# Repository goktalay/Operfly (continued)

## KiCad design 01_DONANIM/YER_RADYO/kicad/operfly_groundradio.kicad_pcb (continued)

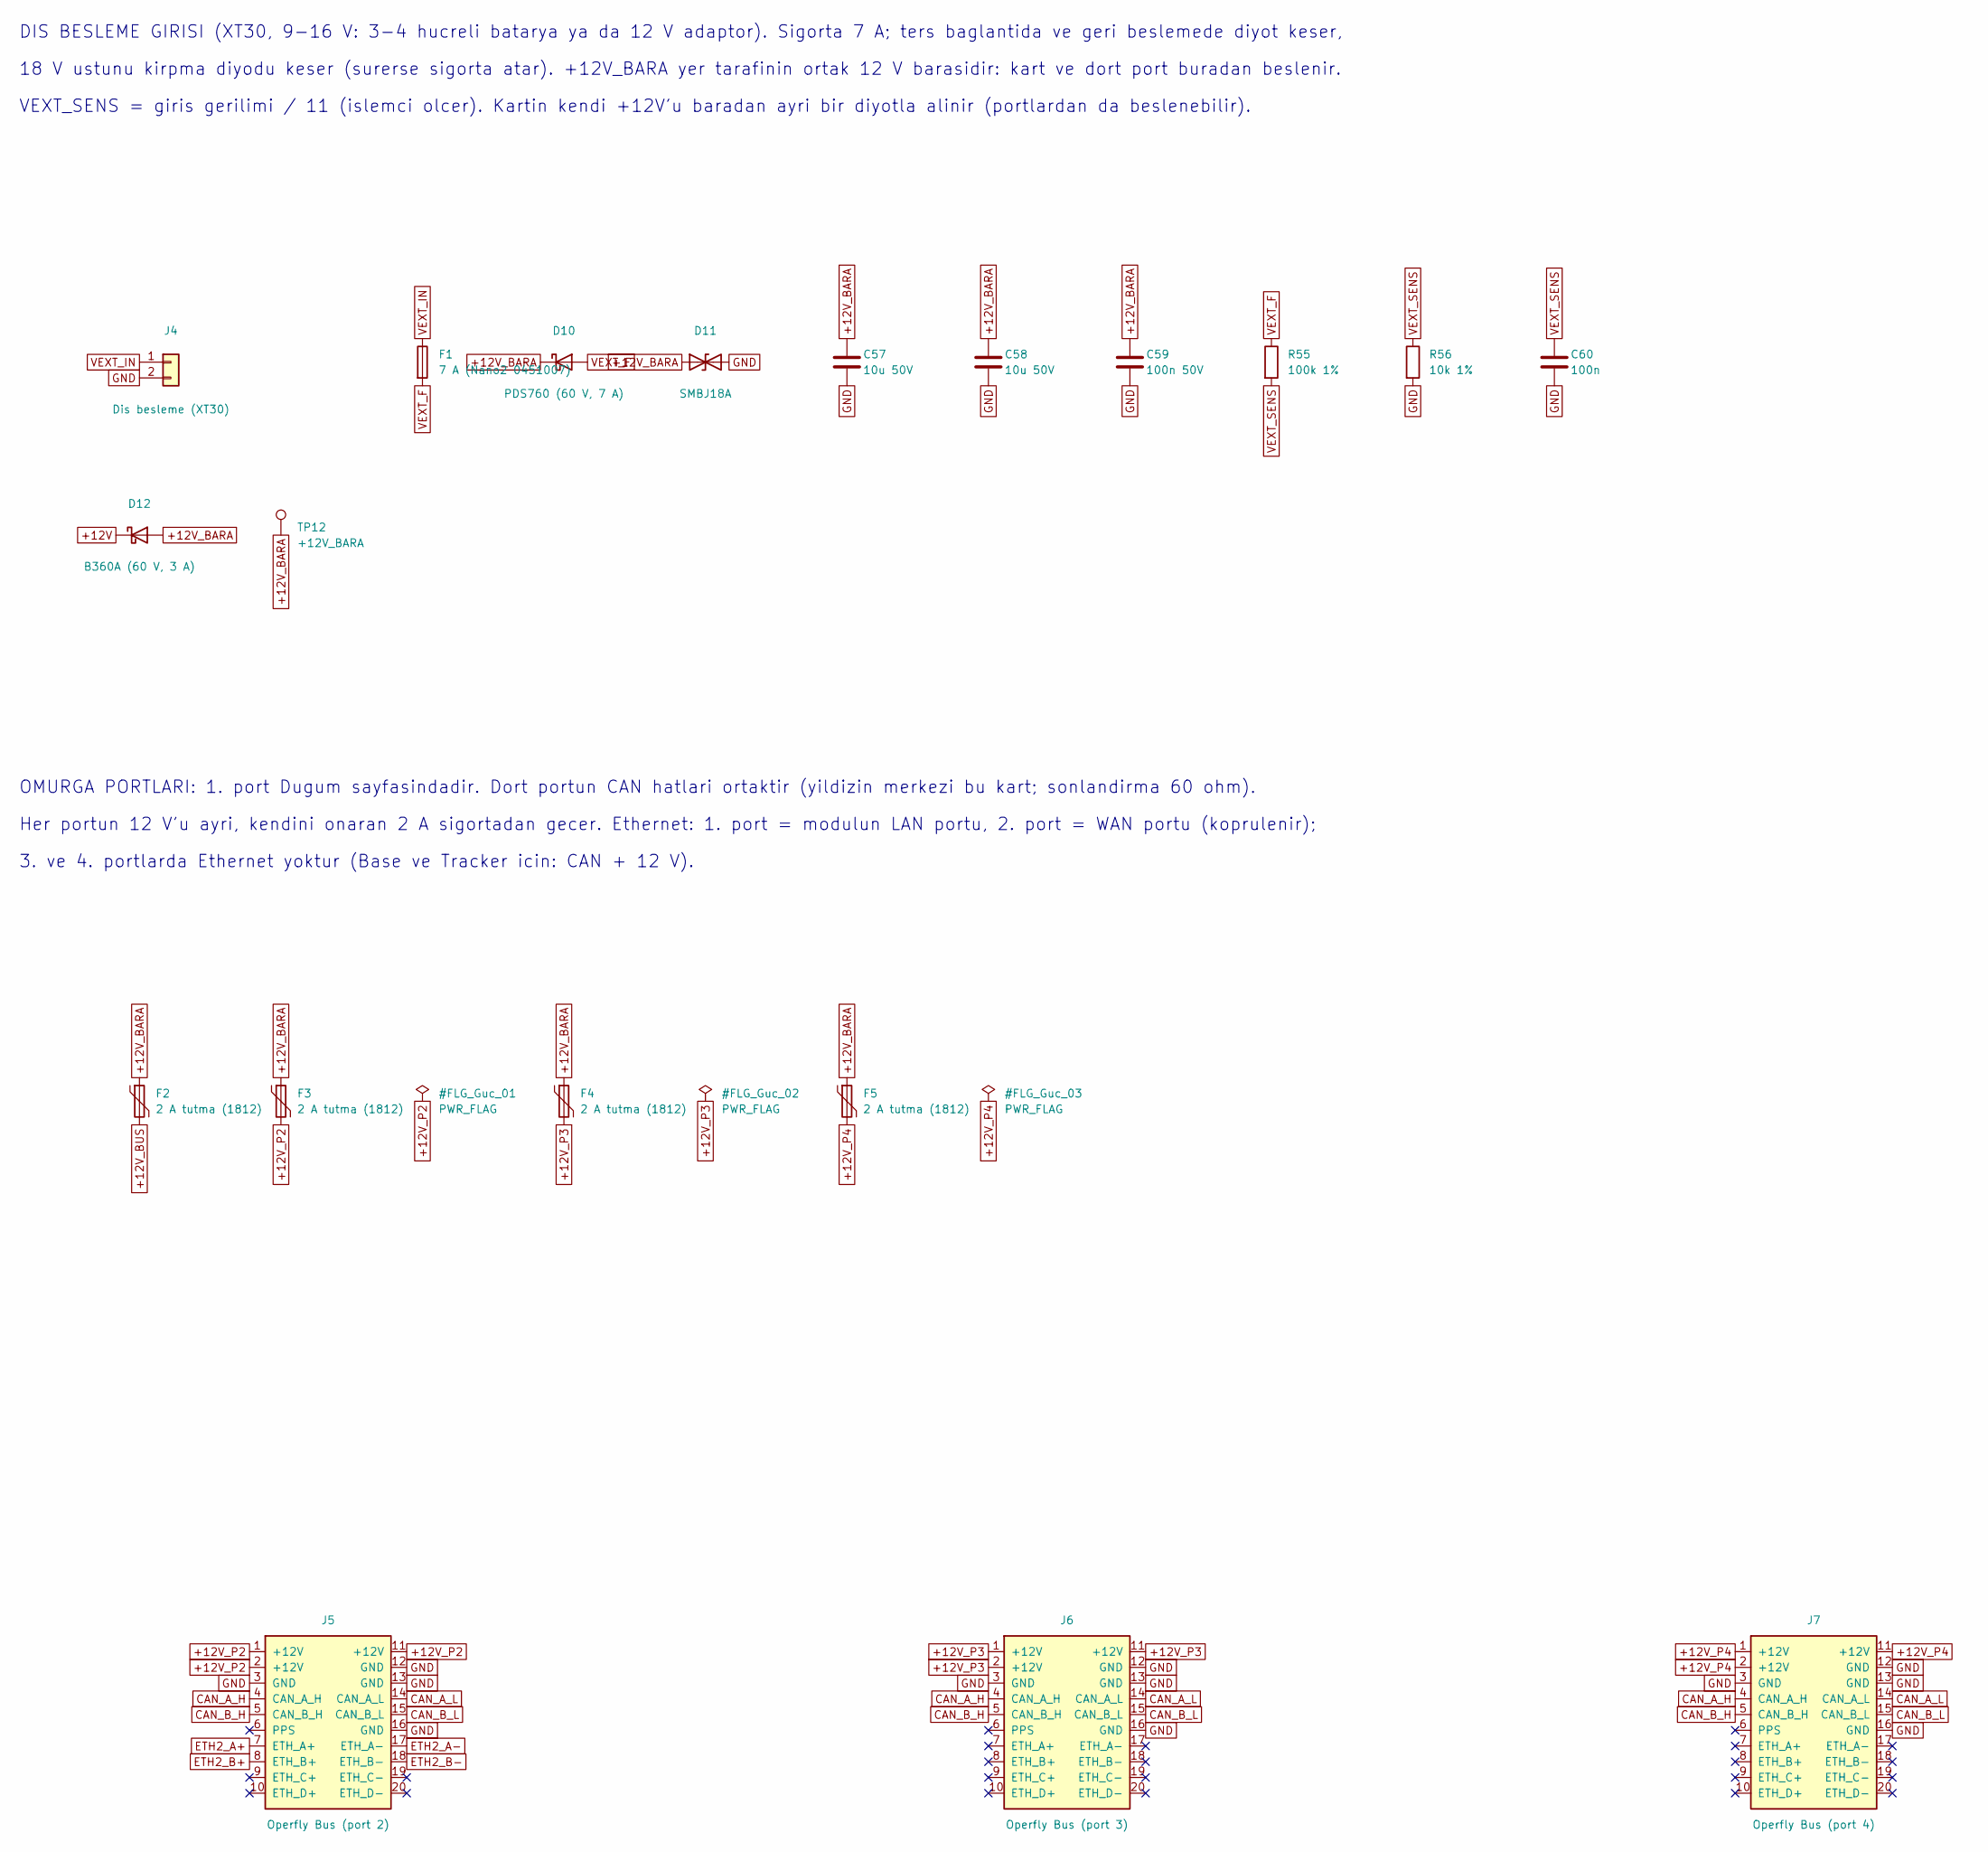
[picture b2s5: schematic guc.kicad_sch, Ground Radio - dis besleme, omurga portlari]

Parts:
C57, C58: 10u 50V; C_1206_3216Metric
C59: 100n 50V; C_0603_1608Metric
C60: 100n; C_0402_1005Metric
D10: PDS760 (60 V, 7 A); D_PowerDI-5
D11: SMBJ18A; D_SMB
D12: B360A (60 V, 3 A); D_SMA
F1: 7 A (Nano2 0451007); Fuse_Littelfuse-NANO2-451_453
F2, F3, F4, F5: 2 A tutma (1812); Fuse_1812_4532Metric
J4: Dis besleme (XT30); AMASS_XT30U-M_1x02_P5.0mm_Vertical
J5: Operfly Bus (port 2); Harwin_Gecko_G125-MS12005M2P_2x10_P1.25mm_Vertical
J6: Operfly Bus (port 3); Harwin_Gecko_G125-MS12005M2P_2x10_P1.25mm_Vertical
J7: Operfly Bus (port 4); Harwin_Gecko_G125-MS12005M2P_2x10_P1.25mm_Vertical
R55: 100k 1%; R_0402_1005Metric
R56: 10k 1%; R_0402_1005Metric
TP12: +12V_BARA; TestPoint_Pad_D1.0mm

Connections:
+12V: D12.1 (K); also elsewhere on the board
+12V_BARA: C57.1, C58.1, C59.1, D10.1 (K), D11.1 (A1), D12.2 (A), F2.1, F3.1, F4.1, F5.1, TP12.1
+12V_BUS: F2.2; also elsewhere on the board
+12V_P2: F3.2, J5.1 (+12V), J5.2 (+12V), J5.11 (+12V)
+12V_P3: F4.2, J6.1 (+12V), J6.2 (+12V), J6.11 (+12V)
+12V_P4: F5.2, J7.1 (+12V), J7.2 (+12V), J7.11 (+12V)
CAN_A_H: J5.4 (CAN_A_H), J6.4 (CAN_A_H), J7.4 (CAN_A_H); also elsewhere on the board
CAN_A_L: J5.14 (CAN_A_L), J6.14 (CAN_A_L), J7.14 (CAN_A_L); also elsewhere on the board
CAN_B_H: J5.5 (CAN_B_H), J6.5 (CAN_B_H), J7.5 (CAN_B_H); also elsewhere on the board
CAN_B_L: J5.15 (CAN_B_L), J6.15 (CAN_B_L), J7.15 (CAN_B_L); also elsewhere on the board
ETH2_A+: J5.7 (ETH_A+); also elsewhere on the board
ETH2_A-: J5.17 (ETH_A-); also elsewhere on the board
ETH2_B+: J5.8 (ETH_B+); also elsewhere on the board
ETH2_B-: J5.18 (ETH_B-); also elsewhere on the board
GND: C57.2, C58.2, C59.2, C60.2, D11.2 (A2), J4.2, J5.3 (GND), J5.12 (GND), J5.13 (GND), J5.16 (GND), J6.3 (GND), J6.12 (GND), J6.13 (GND), J6.16 (GND), J7.3 (GND), J7.12 (GND), J7.13 (GND), J7.16 (GND), R56.2; also elsewhere on the board
VEXT_F: D10.2 (A), F1.2, R55.1
VEXT_IN: F1.1, J4.1
VEXT_SENS: C60.1, R55.2, R56.1; also elsewhere on the board

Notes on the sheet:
VEXT_SENS = giris gerilimi / 11 (islemci olcer). Kartin kendi +12V'u baradan ayri bir diyotla alinir (portlardan da beslenebilir).
Her portun 12 V'u ayri, kendini onaran 2 A sigortadan gecer. Ethernet: 1. port = modulun LAN portu, 2. port = WAN portu (koprulenir);
18 V ustunu kirpma diyodu keser (surerse sigorta atar). +12V_BARA yer tarafinin ortak 12 V barasidir: kart ve dort port buradan beslenir.
3. ve 4. portlarda Ethernet yoktur (Base ve Tracker icin: CAN + 12 V).
DIS BESLEME GIRISI (XT30, 9-16 V: 3-4 hucreli batarya ya da 12 V adaptor). Sigorta 7 A; ters baglantida ve geri beslemede diyot keser,
OMURGA PORTLARI: 1. port Dugum sayfasindadir. Dort portun CAN hatlari ortaktir (yildizin merkezi bu kart; sonlandirma 60 ohm).

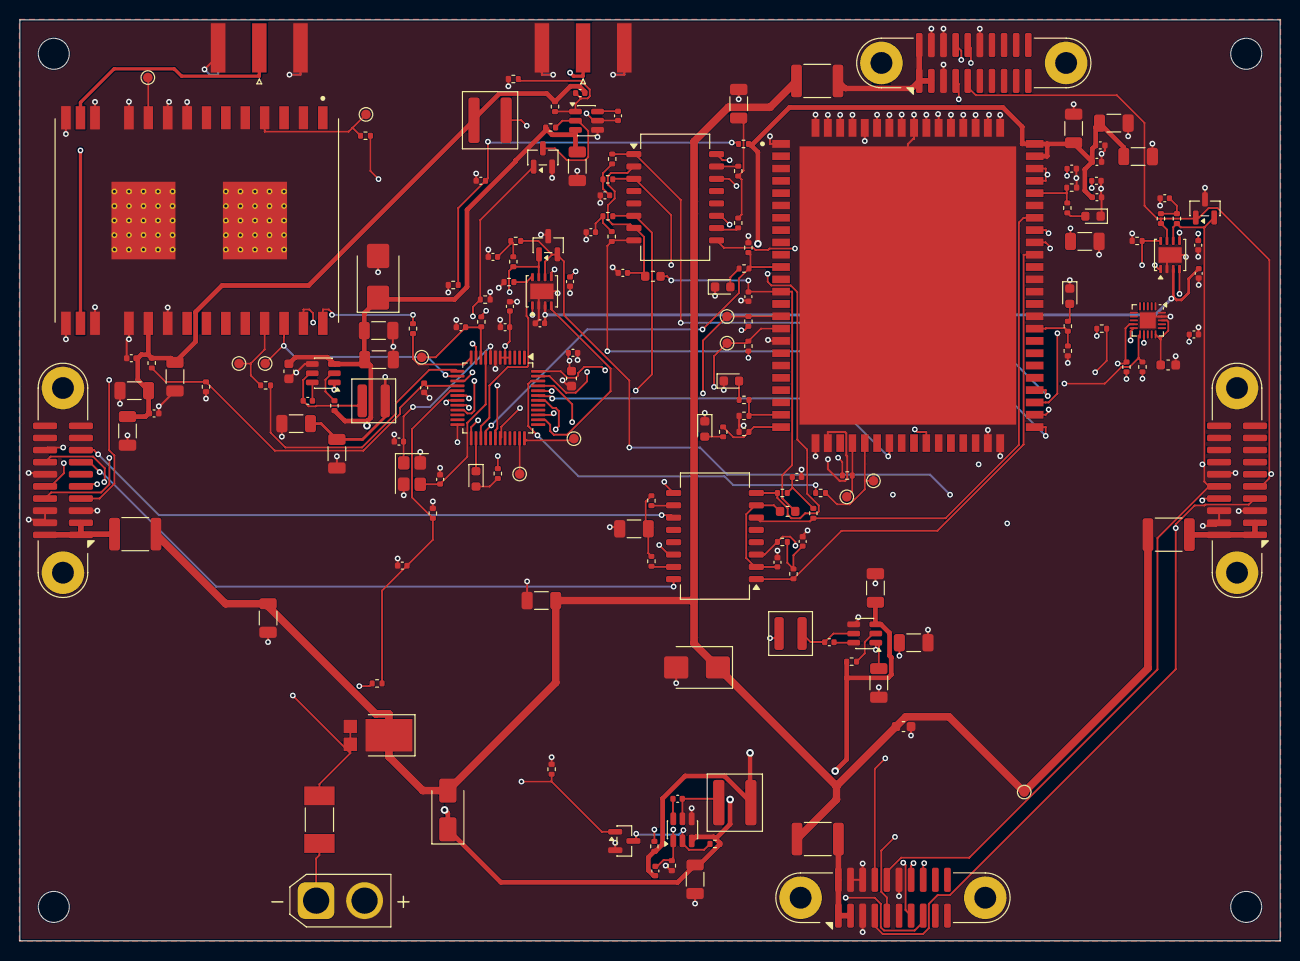
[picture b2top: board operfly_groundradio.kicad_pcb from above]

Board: 6 copper layers, 130.0 x 95.0 mm, 177 parts (0 on the bottom side), 113 nets.

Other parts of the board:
H1, H2, H3, H4: M3; MountingHole_3.2mm_M3

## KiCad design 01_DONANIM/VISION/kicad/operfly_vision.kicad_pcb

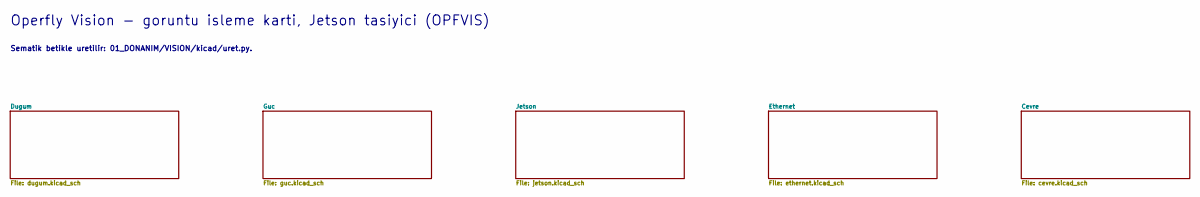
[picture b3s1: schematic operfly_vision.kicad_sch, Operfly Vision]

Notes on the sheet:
Operfly Vision - goruntu isleme karti, Jetson tasiyici (OPFVIS)
Sematik betikle uretilir: 01_DONANIM/VISION/kicad/uret.py.

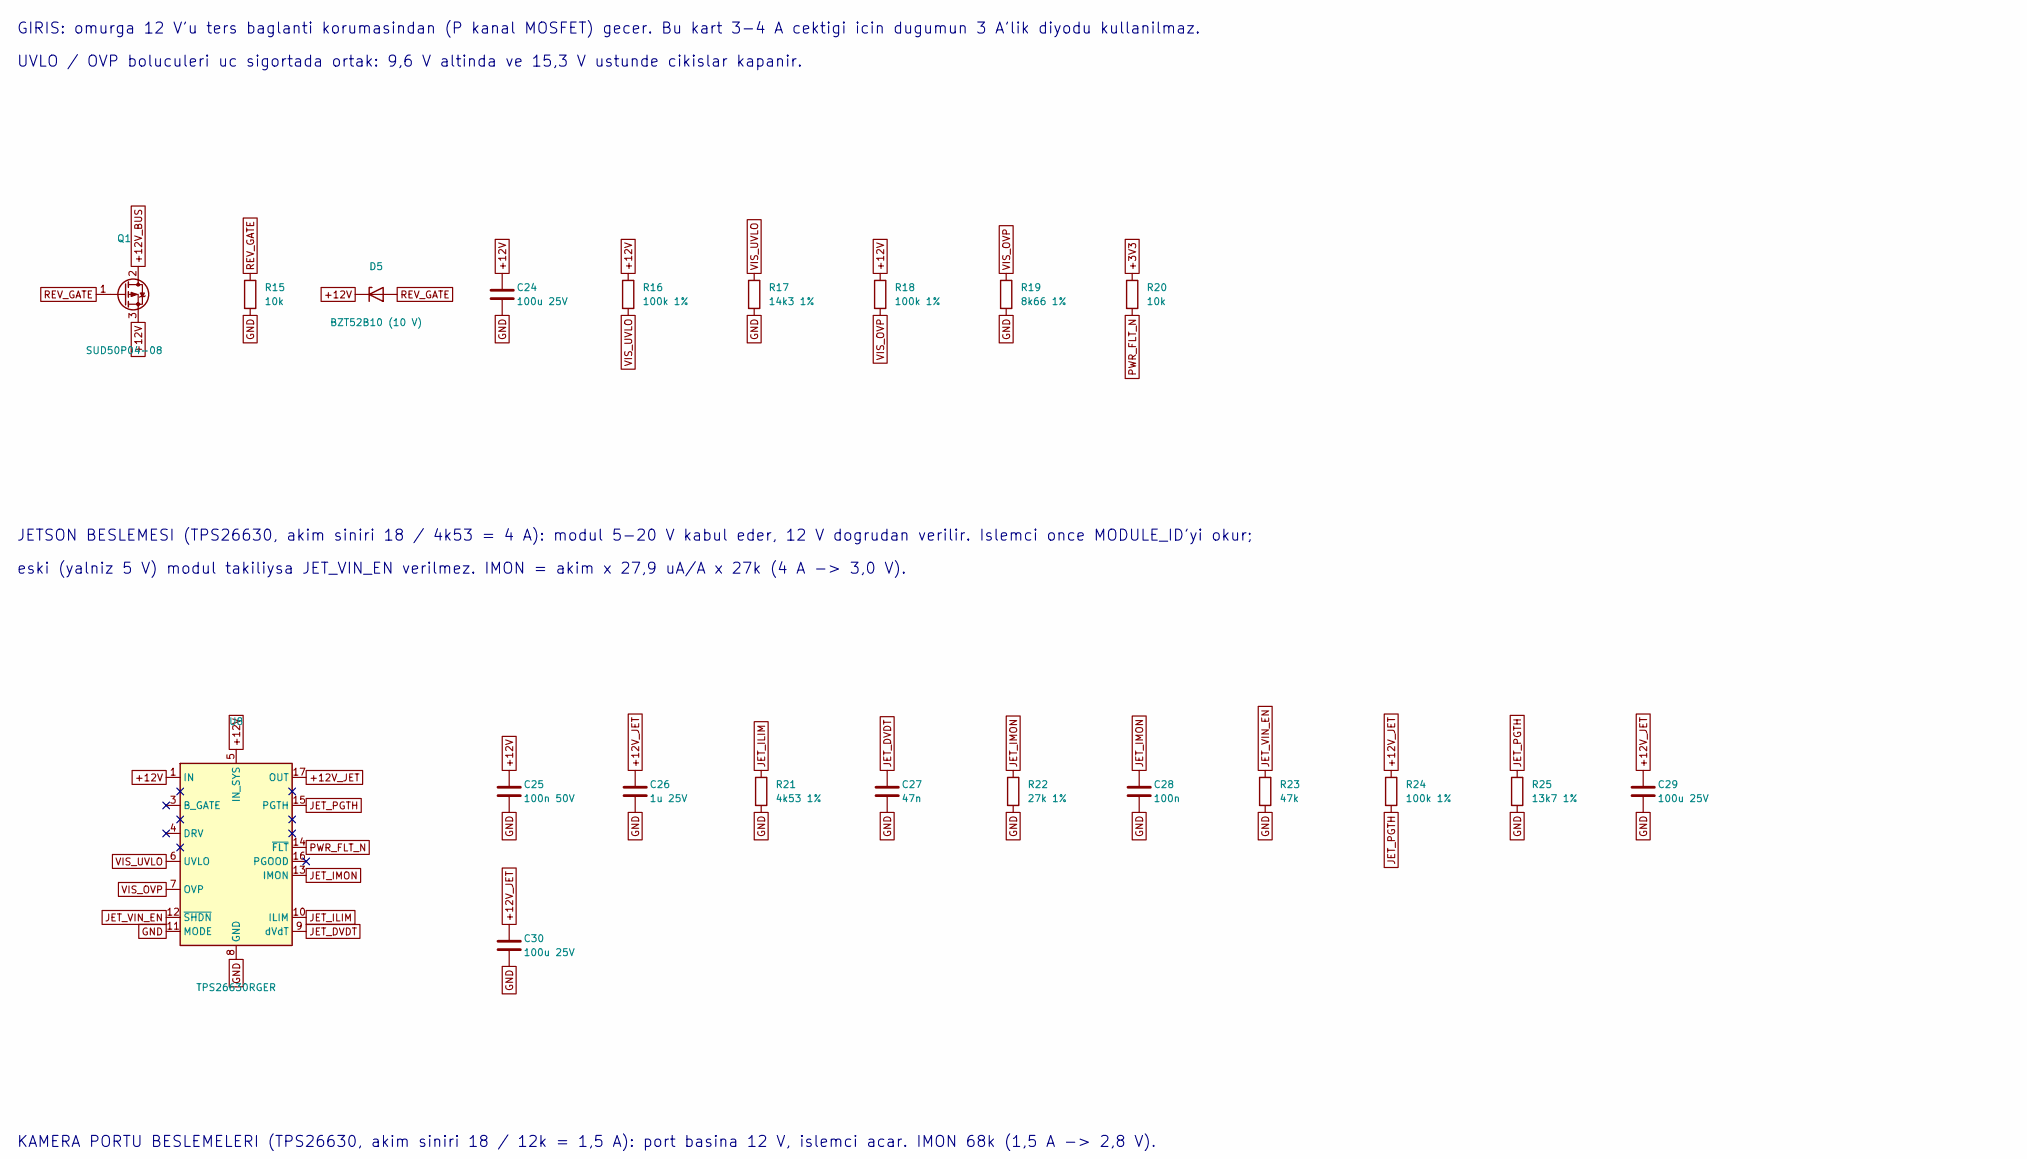
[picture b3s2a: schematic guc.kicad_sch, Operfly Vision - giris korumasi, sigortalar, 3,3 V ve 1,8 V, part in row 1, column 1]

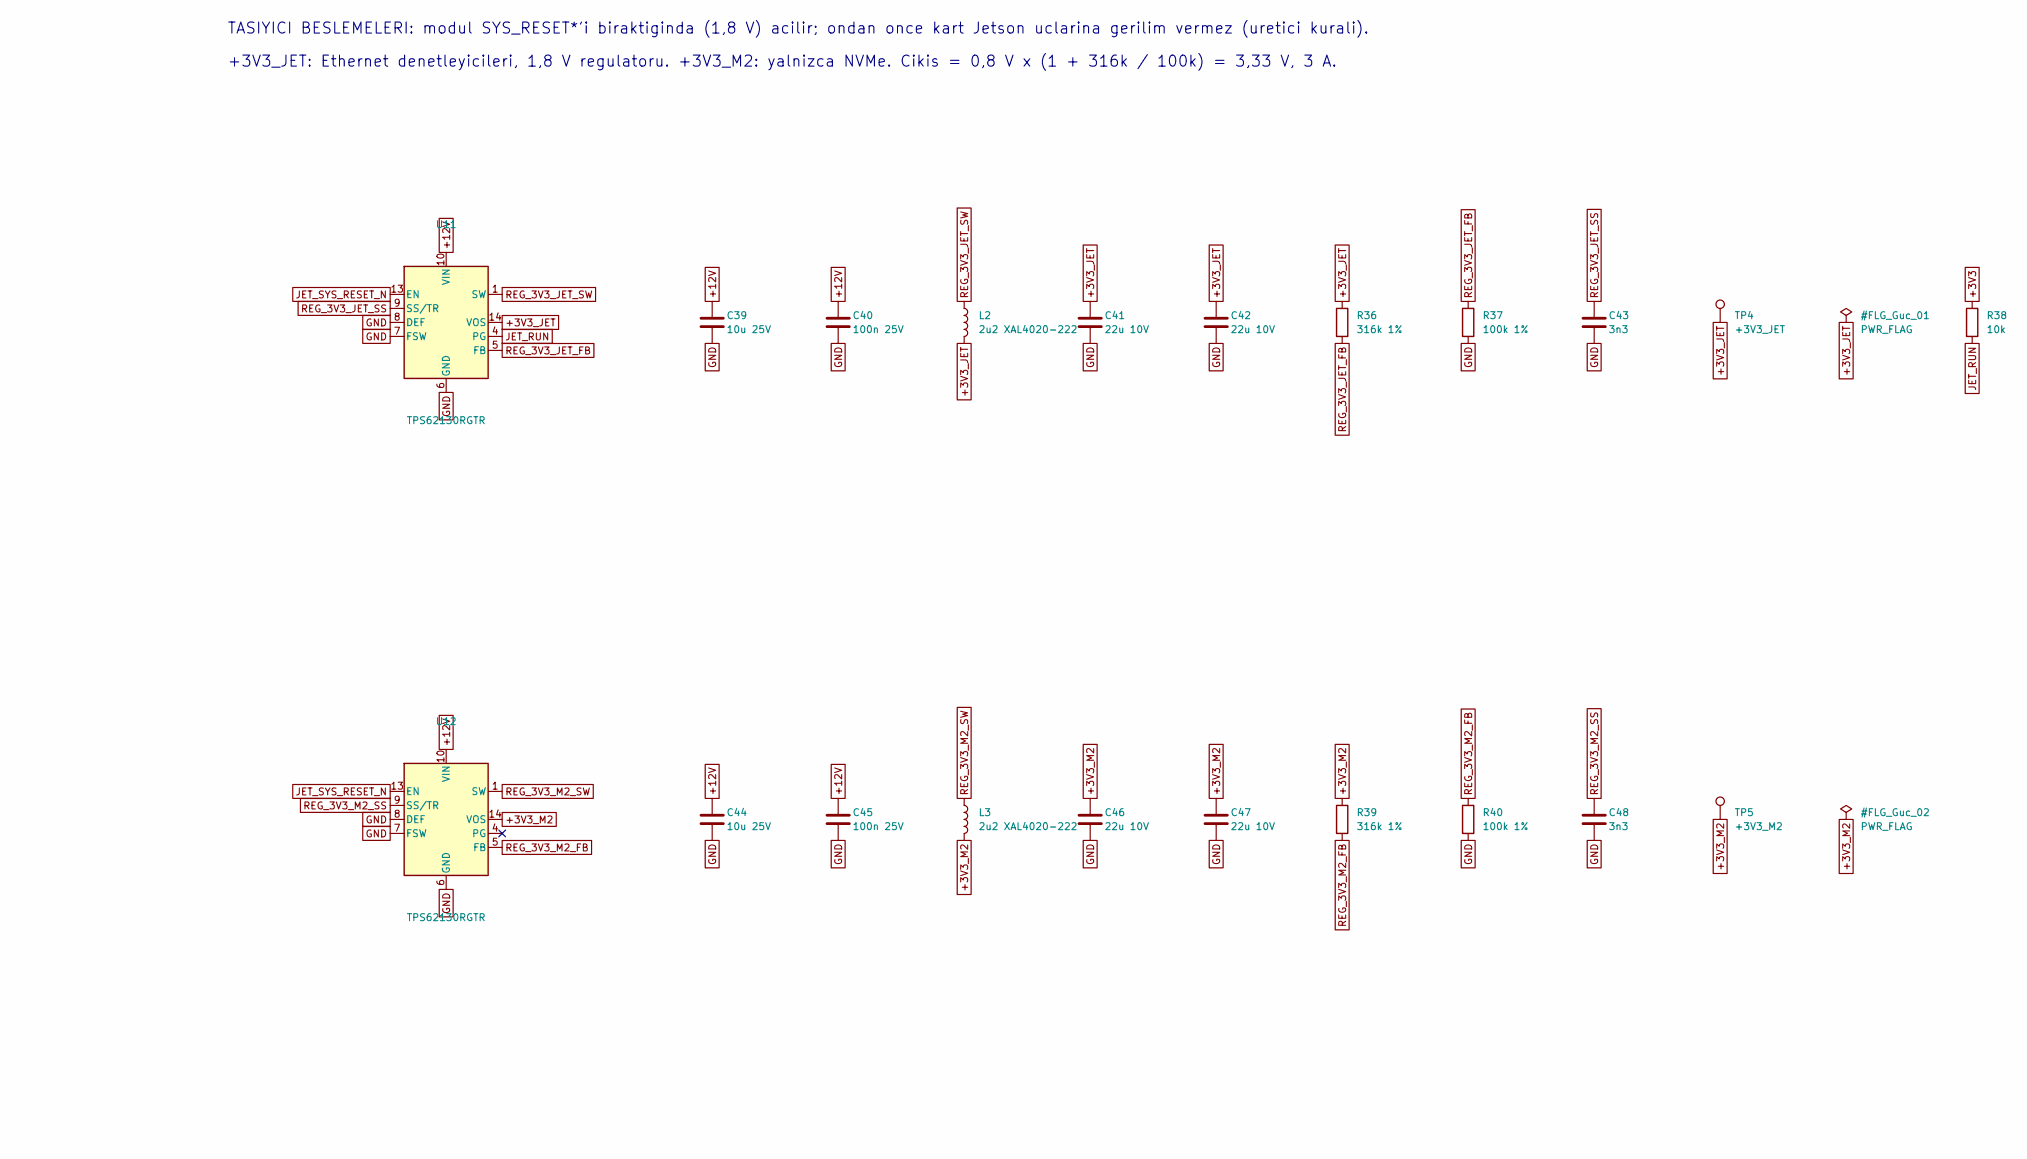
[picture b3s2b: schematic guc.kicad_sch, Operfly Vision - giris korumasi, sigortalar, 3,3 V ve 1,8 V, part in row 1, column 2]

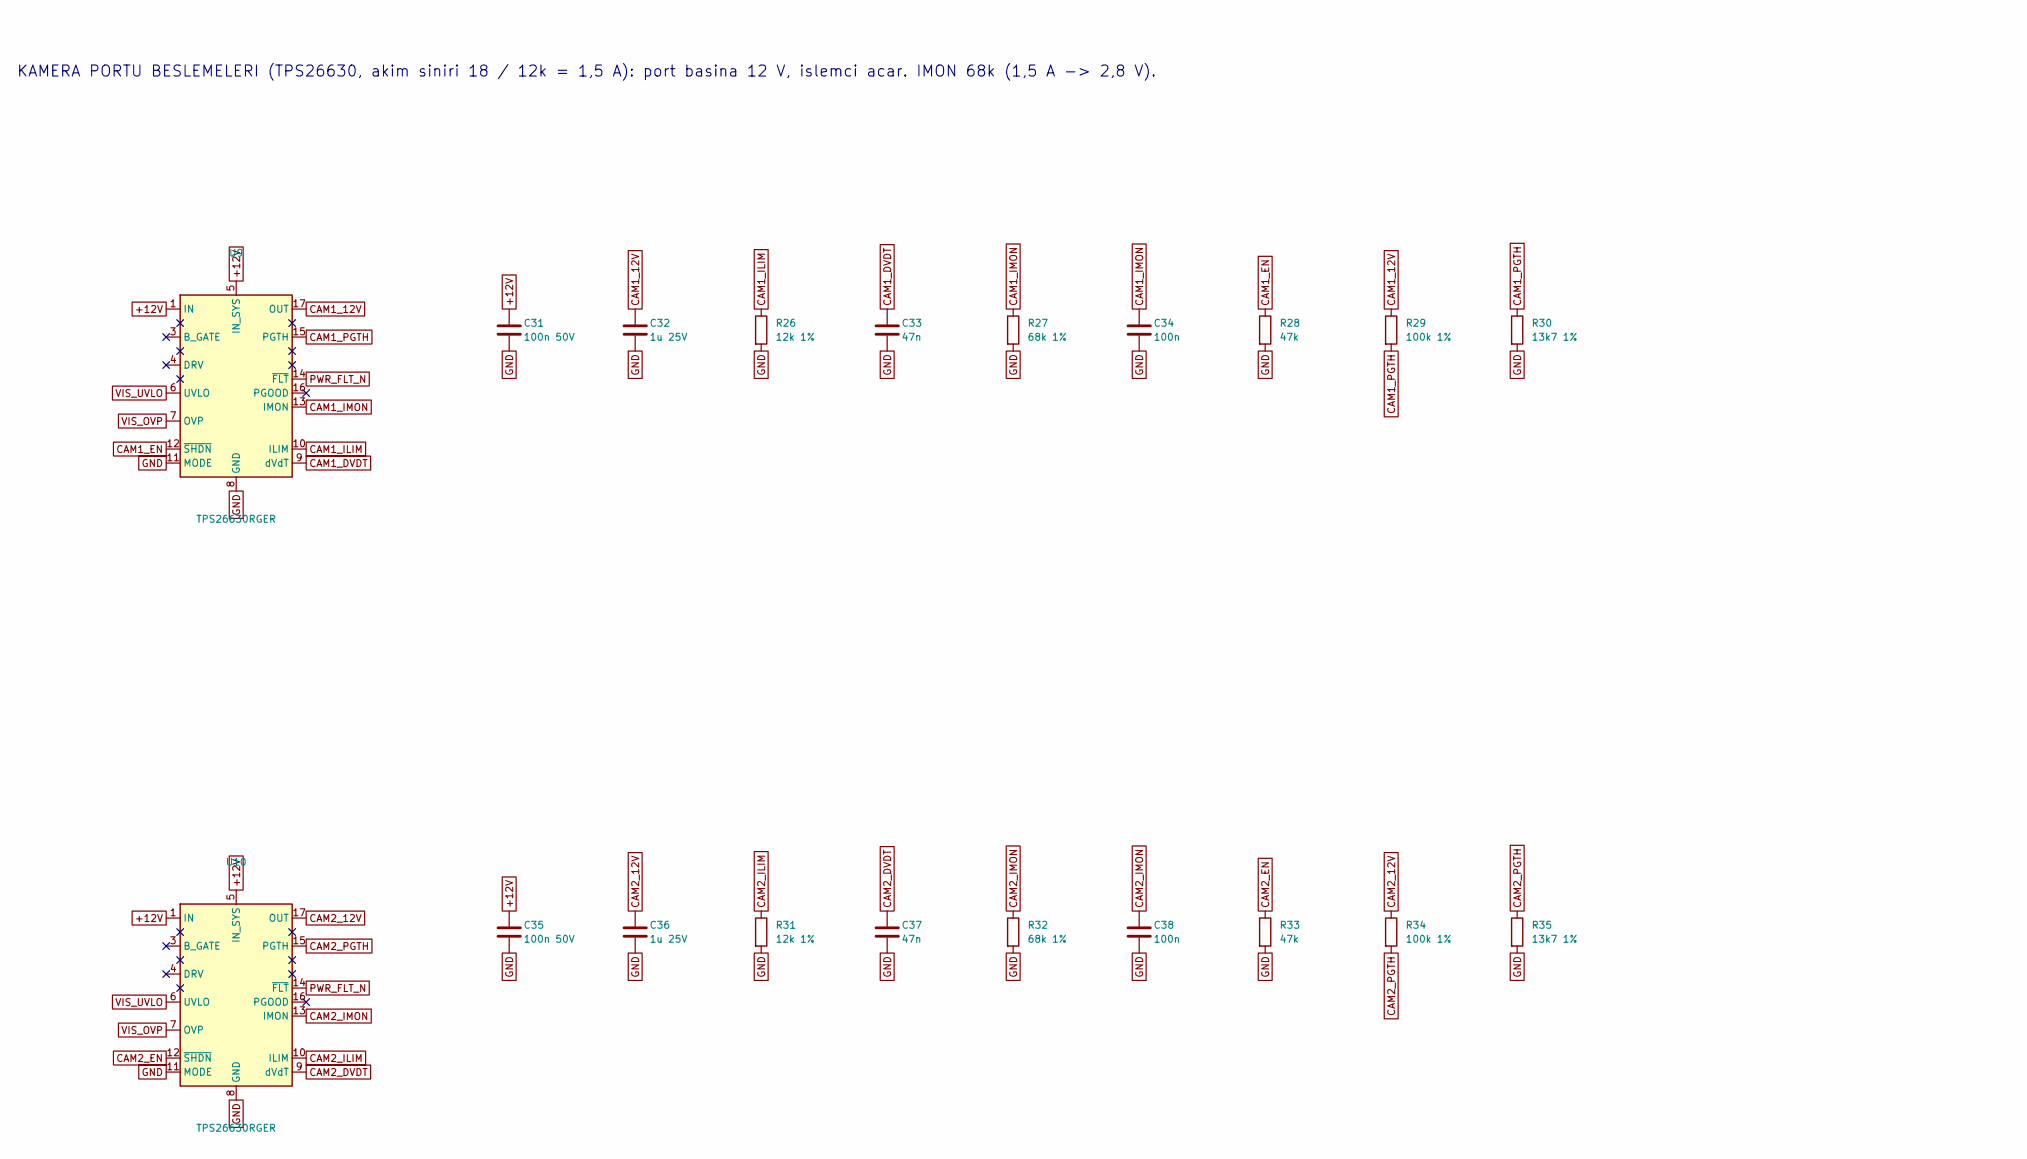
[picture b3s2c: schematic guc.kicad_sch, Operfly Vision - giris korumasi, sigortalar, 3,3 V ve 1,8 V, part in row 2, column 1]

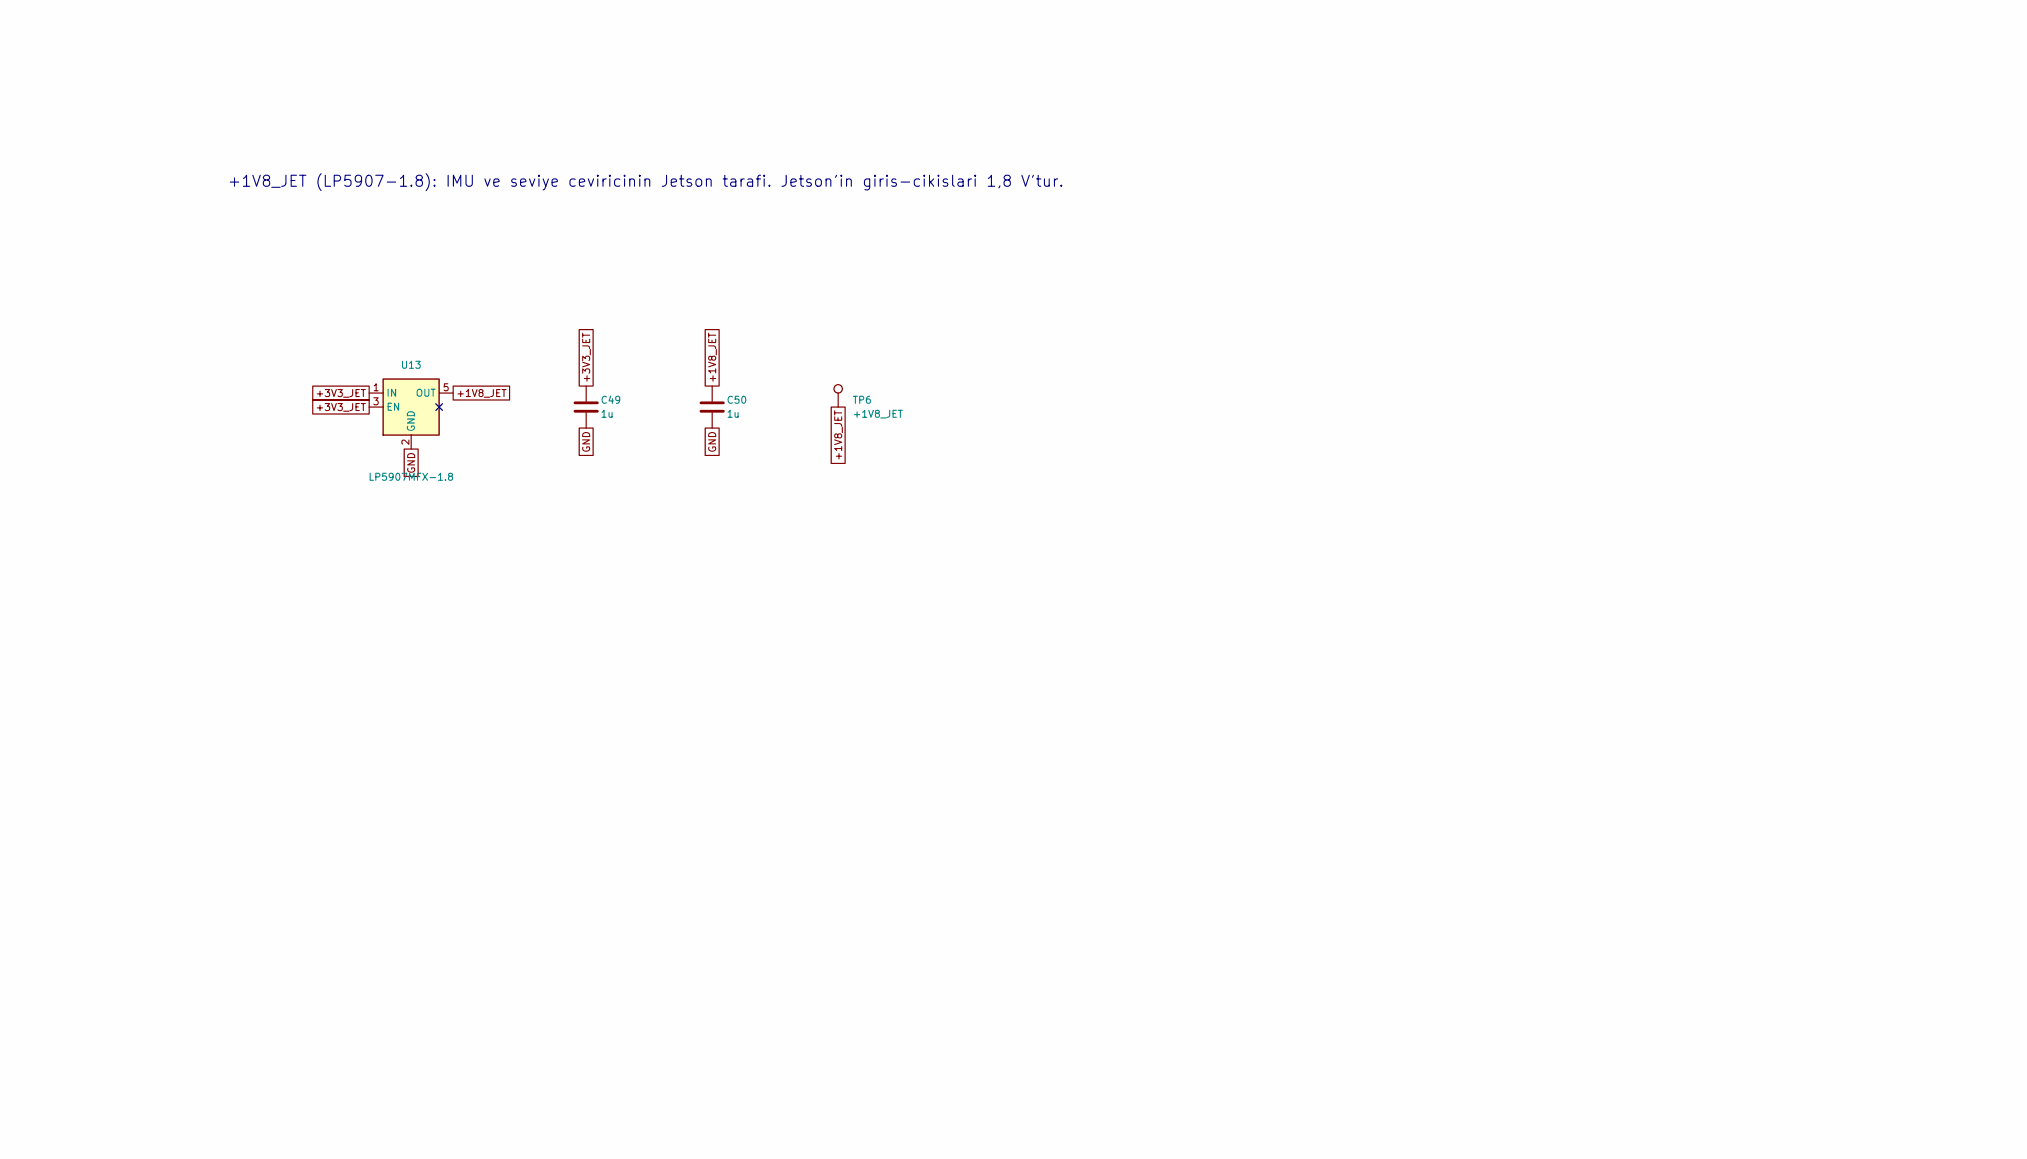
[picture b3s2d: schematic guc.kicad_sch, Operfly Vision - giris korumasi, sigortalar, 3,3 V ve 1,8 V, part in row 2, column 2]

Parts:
C24, C29, C30: 100u 25V; CP_EIA-7343-31_Kemet-D
C25, C31, C35: 100n 50V; C_0603_1608Metric
C26, C32, C36: 1u 25V; C_0603_1608Metric
C27, C33, C37: 47n; C_0402_1005Metric
C28, C34, C38: 100n; C_0402_1005Metric
C39, C44: 10u 25V; C_1206_3216Metric
C40, C45: 100n 25V; C_0603_1608Metric
C41, C42, C46, C47: 22u 10V; C_1206_3216Metric
C43, C48: 3n3; C_0402_1005Metric
C49, C50: 1u; C_0402_1005Metric
D5: BZT52B10 (10 V); D_SOD-123F
L2, L3: 2u2 XAL4020-222; L_Coilcraft_XAL4020-XXX
Q1: SUD50P04-08; TO-252-2
R15, R20, R38: 10k; R_0402_1005Metric
R16, R18, R24, R29, R34, R37, R40: 100k 1%; R_0402_1005Metric
R17: 14k3 1%; R_0402_1005Metric
R19: 8k66 1%; R_0402_1005Metric
R21: 4k53 1%; R_0402_1005Metric
R22: 27k 1%; R_0402_1005Metric
R23, R28, R33: 47k; R_0402_1005Metric
R25, R30, R35: 13k7 1%; R_0402_1005Metric
R26, R31: 12k 1%; R_0402_1005Metric
R27, R32: 68k 1%; R_0402_1005Metric
R36, R39: 316k 1%; R_0402_1005Metric
TP4: +3V3_JET; TestPoint_Pad_D1.0mm
TP5: +3V3_M2; TestPoint_Pad_D1.0mm
TP6: +1V8_JET; TestPoint_Pad_D1.0mm
U8, U9, U10: TPS26630RGER; Texas_RGE0024H_VQFN-24-1EP_4x4mm_P0.5mm_EP2.7x2.7mm_Thermal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
U11, U12: TPS62130RGTR; VQFN-16-1EP_3x3mm_P0.5mm_EP1.68x1.68mm_ThermalVias
U13: LP5907MFX-1.8; SOT-23-5

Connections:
+1V8_JET: C50.1, TP6.1, U13.5 (OUT); also elsewhere on the board
+3V3: R20.1, R38.1; also elsewhere on the board
+3V3_JET: C41.1, C42.1, C49.1, L2.2, R36.1, TP4.1, U11.14 (VOS), U13.1 (IN), U13.3 (EN); also elsewhere on the board
+3V3_M2: C46.1, C47.1, L3.2, R39.1, TP5.1, U12.14 (VOS); also elsewhere on the board
+12V: C24.1, C25.1, C31.1, C35.1, C39.1, C40.1, C44.1, C45.1, D5.1 (K), Q1.3 (S), R16.1, R18.1, U8.1 (IN), U8.2 (IN), U8.5 (IN_SYS), U9.1 (IN), U9.2 (IN), U9.5 (IN_SYS), U10.1 (IN), U10.2 (IN), U10.5 (IN_SYS), U11.10 (VIN), U11.11 (VIN), U11.12 (VIN), U12.10 (VIN), U12.11 (VIN), U12.12 (VIN); also elsewhere on the board
+12V_BUS: Q1.2 (D); also elsewhere on the board
+12V_JET: C26.1, C29.1, C30.1, R24.1, U8.17 (OUT), U8.18 (OUT); also elsewhere on the board
CAM1_12V: C32.1, R29.1, U9.17 (OUT), U9.18 (OUT); also elsewhere on the board
CAM1_DVDT: C33.1, U9.9 (dVdT)
CAM1_EN: R28.1, U9.12 (~SHDN); also elsewhere on the board
CAM1_ILIM: R26.1, U9.10 (ILIM)
CAM1_IMON: C34.1, R27.1, U9.13 (IMON); also elsewhere on the board
CAM1_PGTH: R29.2, R30.1, U9.15 (PGTH)
CAM2_12V: C36.1, R34.1, U10.17 (OUT), U10.18 (OUT); also elsewhere on the board
CAM2_DVDT: C37.1, U10.9 (dVdT)
CAM2_EN: R33.1, U10.12 (~SHDN); also elsewhere on the board
CAM2_ILIM: R31.1, U10.10 (ILIM)
CAM2_IMON: C38.1, R32.1, U10.13 (IMON); also elsewhere on the board
CAM2_PGTH: R34.2, R35.1, U10.15 (PGTH)
GND: C24.2, C25.2, C26.2, C27.2, C28.2, C29.2, C30.2, C31.2, C32.2, C33.2, C34.2, C35.2, C36.2, C37.2, C38.2, C39.2, C40.2, C41.2, C42.2, C43.2, C44.2, C45.2, C46.2, C47.2, C48.2, C49.2, C50.2, R15.2, R17.2, R19.2, R21.2, R22.2, R23.2, R25.2, R26.2, R27.2, R28.2, R30.2, R31.2, R32.2, R33.2, R35.2, R37.2, R40.2, U8.8 (GND), U8.11 (MODE), U8.25 (GND), U9.8 (GND), U9.11 (MODE), U9.25 (GND), U10.8 (GND), U10.11 (MODE), U10.25 (GND), U11.6 (GND), U11.7 (FSW), U11.8 (DEF), U11.15 (GND), U11.16 (GND), U11.17 (GND), U12.6 (GND), U12.7 (FSW), U12.8 (DEF), U12.15 (GND), U12.16 (GND), U12.17 (GND), U13.2 (GND); also elsewhere on the board
JET_DVDT: C27.1, U8.9 (dVdT)
JET_ILIM: R21.1, U8.10 (ILIM)
JET_IMON: C28.1, R22.1, U8.13 (IMON); also elsewhere on the board
JET_PGTH: R24.2, R25.1, U8.15 (PGTH)
JET_RUN: R38.2, U11.4 (PG); also elsewhere on the board
JET_SYS_RESET_N: U11.13 (EN), U12.13 (EN); also elsewhere on the board
JET_VIN_EN: R23.1, U8.12 (~SHDN); also elsewhere on the board
PWR_FLT_N: R20.2, U8.14 (~FLT), U9.14 (~FLT), U10.14 (~FLT); also elsewhere on the board
REG_3V3_JET_FB: R36.2, R37.1, U11.5 (FB)
REG_3V3_JET_SS: C43.1, U11.9 (SS/TR)
REG_3V3_JET_SW: L2.1, U11.1 (SW), U11.2 (SW), U11.3 (SW)
REG_3V3_M2_FB: R39.2, R40.1, U12.5 (FB)
REG_3V3_M2_SS: C48.1, U12.9 (SS/TR)
REG_3V3_M2_SW: L3.1, U12.1 (SW), U12.2 (SW), U12.3 (SW)
REV_GATE: D5.2 (A), Q1.1 (G), R15.1
VIS_OVP: R18.2, R19.1, U8.7 (OVP), U9.7 (OVP), U10.7 (OVP)
VIS_UVLO: R16.2, R17.1, U8.6 (UVLO), U9.6 (UVLO), U10.6 (UVLO)

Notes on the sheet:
KAMERA PORTU BESLEMELERI (TPS26630, akim siniri 18 / 12k = 1,5 A): port basina 12 V, islemci acar. IMON 68k (1,5 A -> 2,8 V).
+3V3_JET: Ethernet denetleyicileri, 1,8 V regulatoru. +3V3_M2: yalnizca NVMe. Cikis = 0,8 V x (1 + 316k / 100k) = 3,33 V, 3 A.
TASIYICI BESLEMELERI: modul SYS_RESET*'i biraktiginda (1,8 V) acilir; ondan once kart Jetson uclarina gerilim vermez (uretici kurali).
UVLO / OVP boluculeri uc sigortada ortak: 9,6 V altinda ve 15,3 V ustunde cikislar kapanir.
+1V8_JET (LP5907-1.8): IMU ve seviye ceviricinin Jetson tarafi. Jetson'in giris-cikislari 1,8 V'tur.
eski (yalniz 5 V) modul takiliysa JET_VIN_EN verilmez. IMON = akim x 27,9 uA/A x 27k (4 A -> 3,0 V).
JETSON BESLEMESI (TPS26630, akim siniri 18 / 4k53 = 4 A): modul 5-20 V kabul eder, 12 V dogrudan verilir. Islemci once MODULE_ID'yi okur;
GIRIS: omurga 12 V'u ters baglanti korumasindan (P kanal MOSFET) gecer. Bu kart 3-4 A cektigi icin dugumun 3 A'lik diyodu kullanilmaz.
